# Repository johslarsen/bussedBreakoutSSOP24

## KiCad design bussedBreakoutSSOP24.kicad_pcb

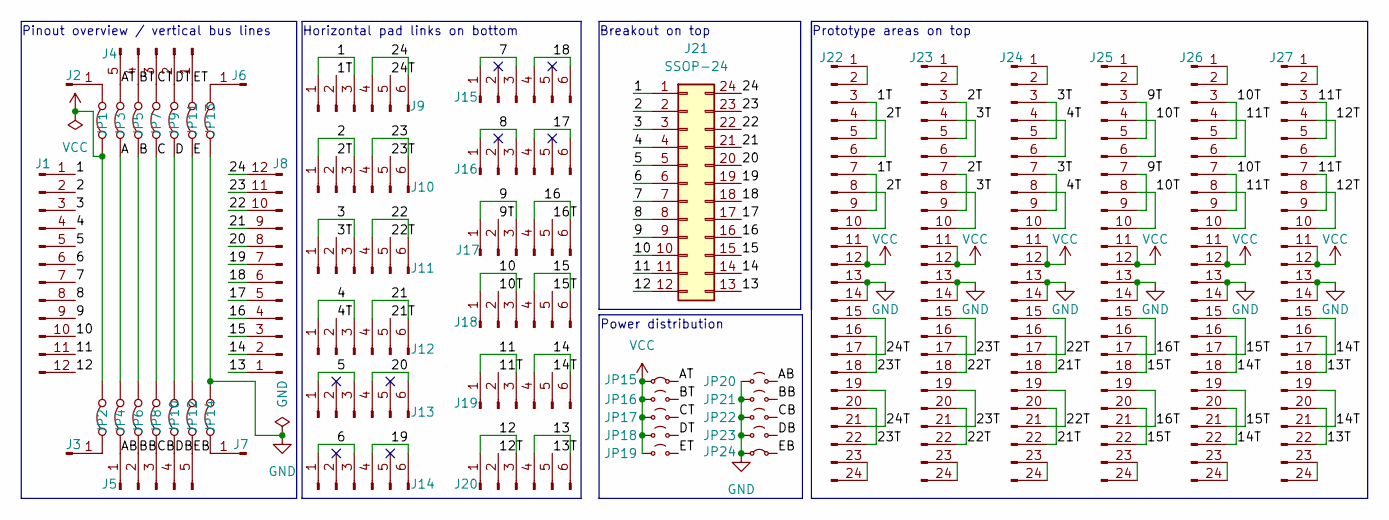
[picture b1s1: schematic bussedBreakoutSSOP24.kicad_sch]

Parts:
J1, J8: Conn_01x12_Pin; Castellated_2x12
J2, J3, J6, J7: Conn_01x01_Pin; Castellated_corner
J4, J5: Conn_01x05_Pin; Castellated_2x05
J9, J10, J11, J12, J13, J14, J15, J16, J17, J18, J19, J20: Conn_01x06_Pin; SMD_0805_grid_1x6
J21: SSOP-24; SSOP-24_3.9-7.5mmx8.2mm_P0.65mm
J22, J23, J24, J25, J26, J27: Conn_01x24_Pin; SMD_grid_2x12_0402
JP1, JP2, JP3, JP4, JP5, JP6, JP7, JP8, JP9, JP10, JP11, JP12, JP13, JP14: Jumper_2_Bridged; SolderJumper-2_0402_Bridged_Unmarked
JP15, JP24: Jumper_2_Small_Bridged; SolderJumper-2_0402_Bridged_Unmarked
JP16, JP17, JP18, JP19, JP20, JP21, JP22, JP23: Jumper_2_Small_Open; SolderJumper-2_0402_Open_Unmarked

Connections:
/1: J1.1, J9.1, J9.3, J21.1
/1T: J9.2, J22.3, J22.5, J22.7, J22.9
/2: J1.2, J10.1, J10.3, J21.2
/2T: J10.2, J22.4, J22.6, J22.8, J22.10, J23.3, J23.5, J23.7, J23.9
/3: J1.3, J11.1, J11.3, J21.3
/3T: J11.2, J23.4, J23.6, J23.8, J23.10, J24.3, J24.5, J24.7, J24.9
/4: J1.4, J12.1, J12.3, J21.4
/4T: J12.2, J24.4, J24.6, J24.8, J24.10
/5: J1.5, J13.1, J13.3, J21.5
/6: J1.6, J14.1, J14.3, J21.6
/7: J1.7, J15.1, J15.3, J21.7
/8: J1.8, J16.1, J16.3, J21.8
/9: J1.9, J17.1, J17.3, J21.9
/9T: J17.2, J25.3, J25.5, J25.7, J25.9
/10: J1.10, J18.1, J18.3, J21.10
/10T: J18.2, J25.4, J25.6, J25.8, J25.10, J26.3, J26.5, J26.7, J26.9
/11: J1.11, J19.1, J19.3, J21.11
/11T: J19.2, J26.4, J26.6, J26.8, J26.10, J27.3, J27.5, J27.7, J27.9
/12: J1.12, J20.1, J20.3, J21.12
/12T: J20.2, J27.4, J27.6, J27.8, J27.10
/13: J8.1, J20.4, J20.6, J21.13
/13T: J20.5, J27.16, J27.18, J27.20, J27.22
/14: J8.2, J19.4, J19.6, J21.14
/14T: J19.5, J26.16, J26.18, J26.20, J26.22, J27.15, J27.17, J27.19, J27.21
/15: J8.3, J18.4, J18.6, J21.15
/15T: J18.5, J25.16, J25.18, J25.20, J25.22, J26.15, J26.17, J26.19, J26.21
/16: J8.4, J17.4, J17.6, J21.16
/16T: J17.5, J25.15, J25.17, J25.19, J25.21
/17: J8.5, J16.4, J16.6, J21.17
/18: J8.6, J15.4, J15.6, J21.18
/19: J8.7, J14.4, J14.6, J21.19
/20: J8.8, J13.4, J13.6, J21.20
/21: J8.9, J12.4, J12.6, J21.21
/21T: J12.5, J24.16, J24.18, J24.20, J24.22
/22: J8.10, J11.4, J11.6, J21.22
/22T: J11.5, J23.16, J23.18, J23.20, J23.22, J24.15, J24.17, J24.19, J24.21
/23: J8.11, J10.4, J10.6, J21.23
/23T: J10.5, J22.16, J22.18, J22.20, J22.22, J23.15, J23.17, J23.19, J23.21
/24: J8.12, J9.4, J9.6, J21.24
/24T: J9.5, J22.15, J22.17, J22.19, J22.21
/A: JP3.1 (A), JP4.2 (B)
/AB: J5.1, JP4.1 (A), JP20.2 (B)
/AT: J4.5, JP3.2 (B), JP15.2 (B)
/B: JP5.1 (A), JP6.2 (B)
/BB: J5.2, JP6.1 (A), JP21.2 (B)
/BT: J4.4, JP5.2 (B), JP16.2 (B)
/C: JP7.1 (A), JP8.2 (B)
/CB: J5.3, JP8.1 (A), JP22.2 (B)
/CT: J4.3, JP7.2 (B), JP17.2 (B)
/D: JP9.1 (A), JP10.2 (B)
/DB: J5.4, JP10.1 (A), JP23.2 (B)
/DT: J4.2, JP9.2 (B), JP18.2 (B)
/E: JP11.1 (A), JP12.2 (B)
/EB: J5.5, JP12.1 (A), JP24.2 (B)
/ET: J4.1, JP11.2 (B), JP19.2 (B)
GND: J22.13, J22.14, J23.13, J23.14, J24.13, J24.14, J25.13, J25.14, J26.13, J26.14, J27.13, J27.14, JP13.1 (A), JP14.2 (B), JP20.1 (A), JP21.1 (A), JP22.1 (A), JP23.1 (A), JP24.1 (A)
unnamed: J2.1, JP1.2 (B)
unnamed: J3.1, JP2.1 (A)
unnamed: J6.1, JP13.2 (B)
unnamed: J7.1, JP14.1 (A)
unnamed: J22.1, J22.2
unnamed: J22.23, J22.24
unnamed: J23.1, J23.2
unnamed: J23.23, J23.24
unnamed: J24.1, J24.2
unnamed: J24.23, J24.24
unnamed: J25.1, J25.2
unnamed: J25.23, J25.24
unnamed: J26.1, J26.2
unnamed: J26.23, J26.24
unnamed: J27.1, J27.2
unnamed: J27.23, J27.24
VCC: J22.11, J22.12, J23.11, J23.12, J24.11, J24.12, J25.11, J25.12, J26.11, J26.12, J27.11, J27.12, JP1.1 (A), JP2.2 (B), JP15.1 (A), JP16.1 (A), JP17.1 (A), JP18.1 (A), JP19.1 (A)

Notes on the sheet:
Pinout overview / vertical bus lines
Power distribution
Prototype areas on top
Horizontal pad links on bottom
Breakout on top

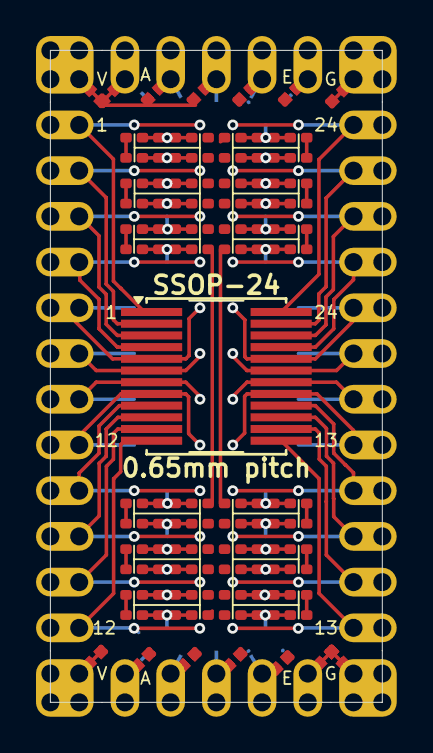
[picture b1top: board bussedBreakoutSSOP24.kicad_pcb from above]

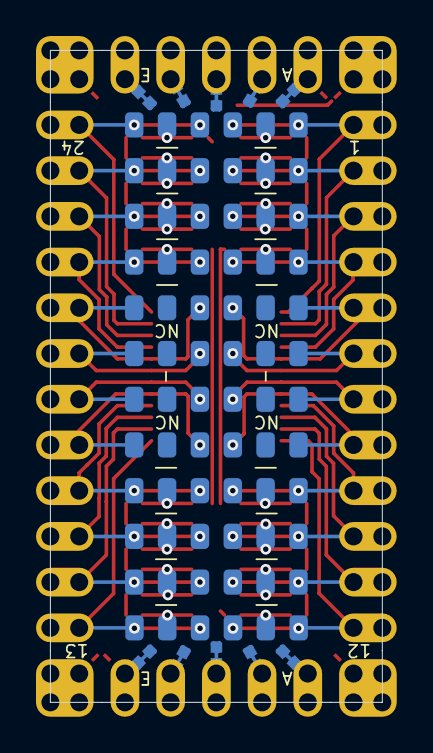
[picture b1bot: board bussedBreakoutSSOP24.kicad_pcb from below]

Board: 2 copper layers, 18.4 x 36.2 mm, 51 parts (26 on the bottom side), 73 nets.

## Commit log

2025-05-01 Change to SSOP24 breakout
2025-05-01 Reorient power distribution jumpers to remove GND/VCC routing workaround
2025-05-01 Fix missing T24/T23 vias
2025-05-01 Fix/exclude DRC errors
